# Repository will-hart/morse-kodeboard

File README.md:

# Morse Kodeboard

I can type 1,250 words per minute on a keyboard with only the minor side effects
of deafening people within 50 meters and wearing out the delete key inside a week.
It occurs to me that If a TKL keyboard makes me 82.24563x more of an engineer,
then how much more engineer would you become by removing 86 of the other keys?

Of course disruption requires innovation, and clearly you can't be a 1,000,000x
engineer with just an "a" key. I considered using an LLM to interpret my intentions
from the velocity and anger with which the key was pressed, but then after a
period of quiet reflection I realised training an AI to do this would immediately
make it sentient.

So to save all of humanity from an AI overlord, I instead applied my vast and
terrifying engineering skills to come up with something the likes of which
has never been seen before. This technological marvel is both simple and truly
disruptive. I invented the idea of using a sequence of long and short pulses to
represent the characters I want to type. I decided to call it a "Morse" coding
sequence, named after [Inspector Morse](https://www.imdb.com/title/tt0092379/)
because I once lived somewhere where an episode was filmed.

This new type of keyboard is clearly more than a keyboard, as without it being
a 1,000,000x engineer clearly isn't possible. So in honor of the great Inspector,
I will call this marvel of modern science a

> **Morse Kodeboard**.

## TLDR

Somehow somebody thought of this idea and I though it would be fun. This is (rust)
firmware for a RP Pico that uses a ~single button~ three buttons and morse code
and pretends to be a USB HID keyboard. Technically it doesn't have a delete button
so good luck if you morse code wrong, which is highly likely because I don't even
know morse code.

## License

* Software: MIT or Apache 2.0
* Hardware: CERN Open Hardware 2.0 - Permissive

## Things I (re/)learned while doing this

- USB Descriptors are always a pain, but I guess with embassy its kind of straightforward?
- Most embassy examples don't use tasks for USB. Its because the code is messier
  as you need to make a lot of the descriptor buffers etc `static`. Using
  `StaticCell` was pretty handy here (there was one embassy example).
- Wireshark + USBpcap are your friend! (although its still tricky working out which
  interface you're meant to look at in Windows).
  - Filter messages to a specific address using `usb.addr[0:4] == "1.1."`
- Make sure to throttle loops, this was the cause of the keyboard not being recognised
  as the USB listening loop was running without any throttling.

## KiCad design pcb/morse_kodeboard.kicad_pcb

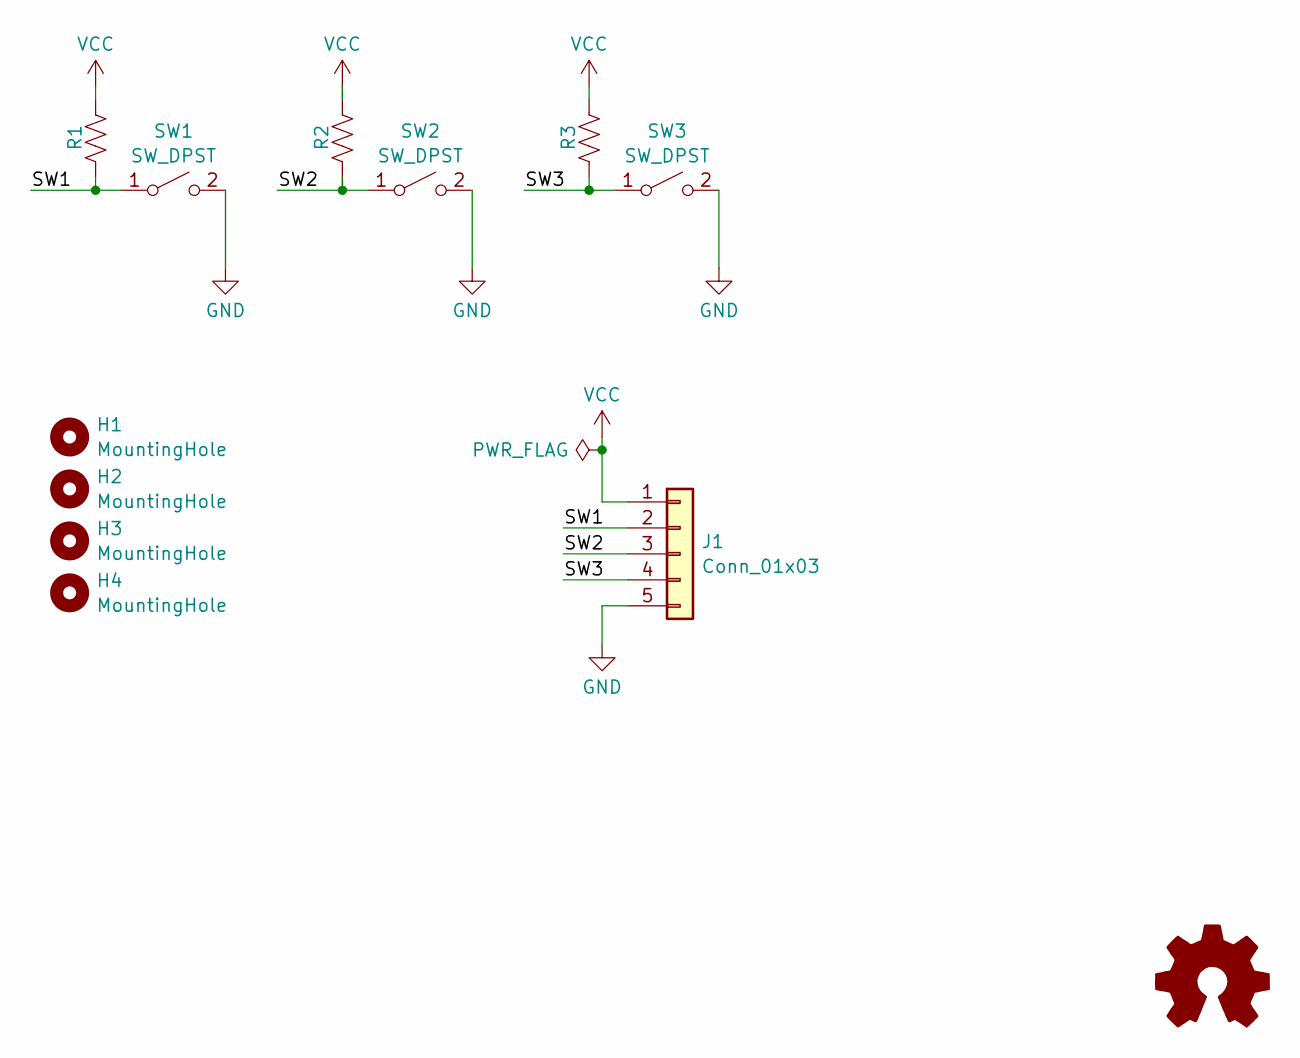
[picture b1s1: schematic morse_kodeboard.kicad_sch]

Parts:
H1, H2, H3, H4: MountingHole; MountingHole_2.2mm_M2
J1: Conn_01x03; JST_PH_S5B-PH-K_1x05_P2.00mm_Horizontal
R1, R2, R3: R_US; R_0805_2012Metric_Pad1.20x1.40mm_HandSolder
SW1, SW2, SW3: SW_DPST; SW_Hotswap_Kailh_MX_1.00u
SYM1: Logo_Open_Hardware_Small; OSHW-Logo2_7.3x6mm_Copper

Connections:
/SW1: J1.2, R1.2, SW1.1 (A)
/SW2: J1.3, R2.2, SW2.1 (A)
/SW3: J1.4, R3.2, SW3.1 (A)
GND: J1.5, SW1.2 (B), SW2.2 (B), SW3.2 (B)
VCC: J1.1, R1.1, R2.1, R3.1

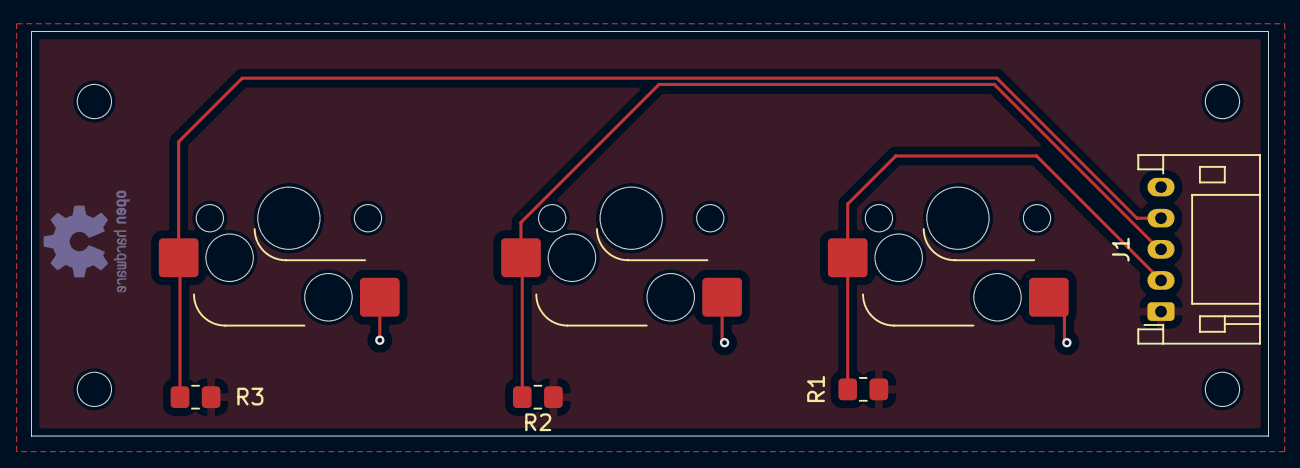
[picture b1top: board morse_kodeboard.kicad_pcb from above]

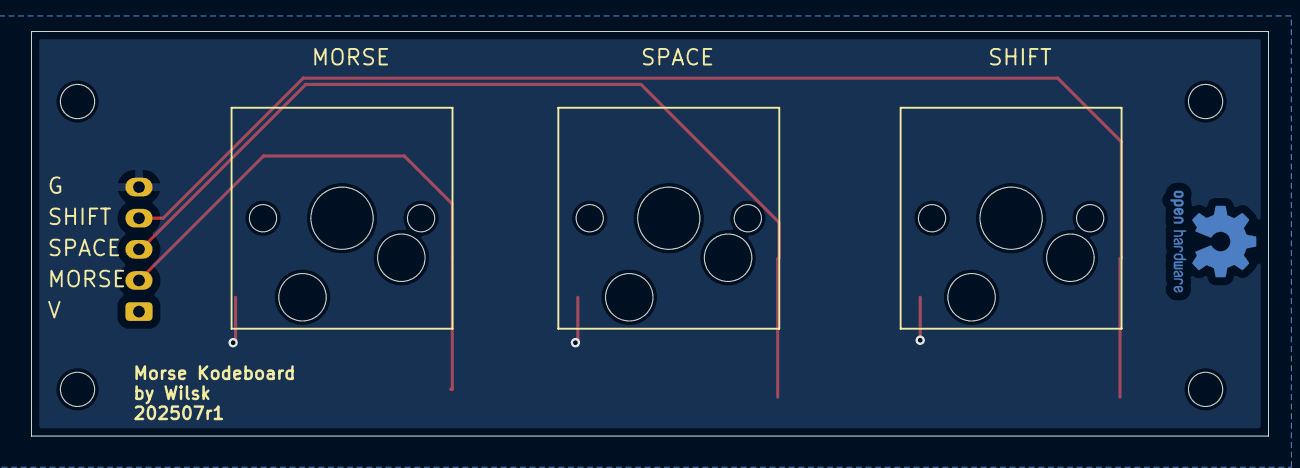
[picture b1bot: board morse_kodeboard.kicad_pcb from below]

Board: 2 copper layers, 79.5 x 26.0 mm, 12 parts (4 on the bottom side), 5 nets.

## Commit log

2025-07-02 Attributes
2025-07-04 Implement morse code decoder
    This is still all untested :D
2025-07-04 Add README
2025-07-04 Add code license
2025-07-04 Hardware License
2025-07-06 Update device details + more logging
2025-07-06 Move into tasks
    Device still not recognised, doing the usual descriptor vs me fight
2025-07-06 Throttle the USB sending loop
    This seemed to block any comms with the host PC, now it works
2025-07-06 Add some notes in the README
2025-07-06 PCB "design"
2025-07-07 Mostly working!
    The decoder is a bit weird, but it could be me being slow.
    Probably going to write my own
2025-07-07 Make PCB single button
2025-07-07 Implement own decoder - Working!
2025-07-07 More speed!
2025-07-07 Update PCB files with three buttons.
    Sent off to fab as r1!
2025-07-07 Add shift button, placeholder for space
2025-07-07 Update logging for shift key
2025-07-08 Implement space key
2025-07-08 Make shift key actually Capslock
2025-07-20 Rev 1 PCB
2025-07-20 Update README for rev 1
2025-07-21 Fix 'w' decoding
